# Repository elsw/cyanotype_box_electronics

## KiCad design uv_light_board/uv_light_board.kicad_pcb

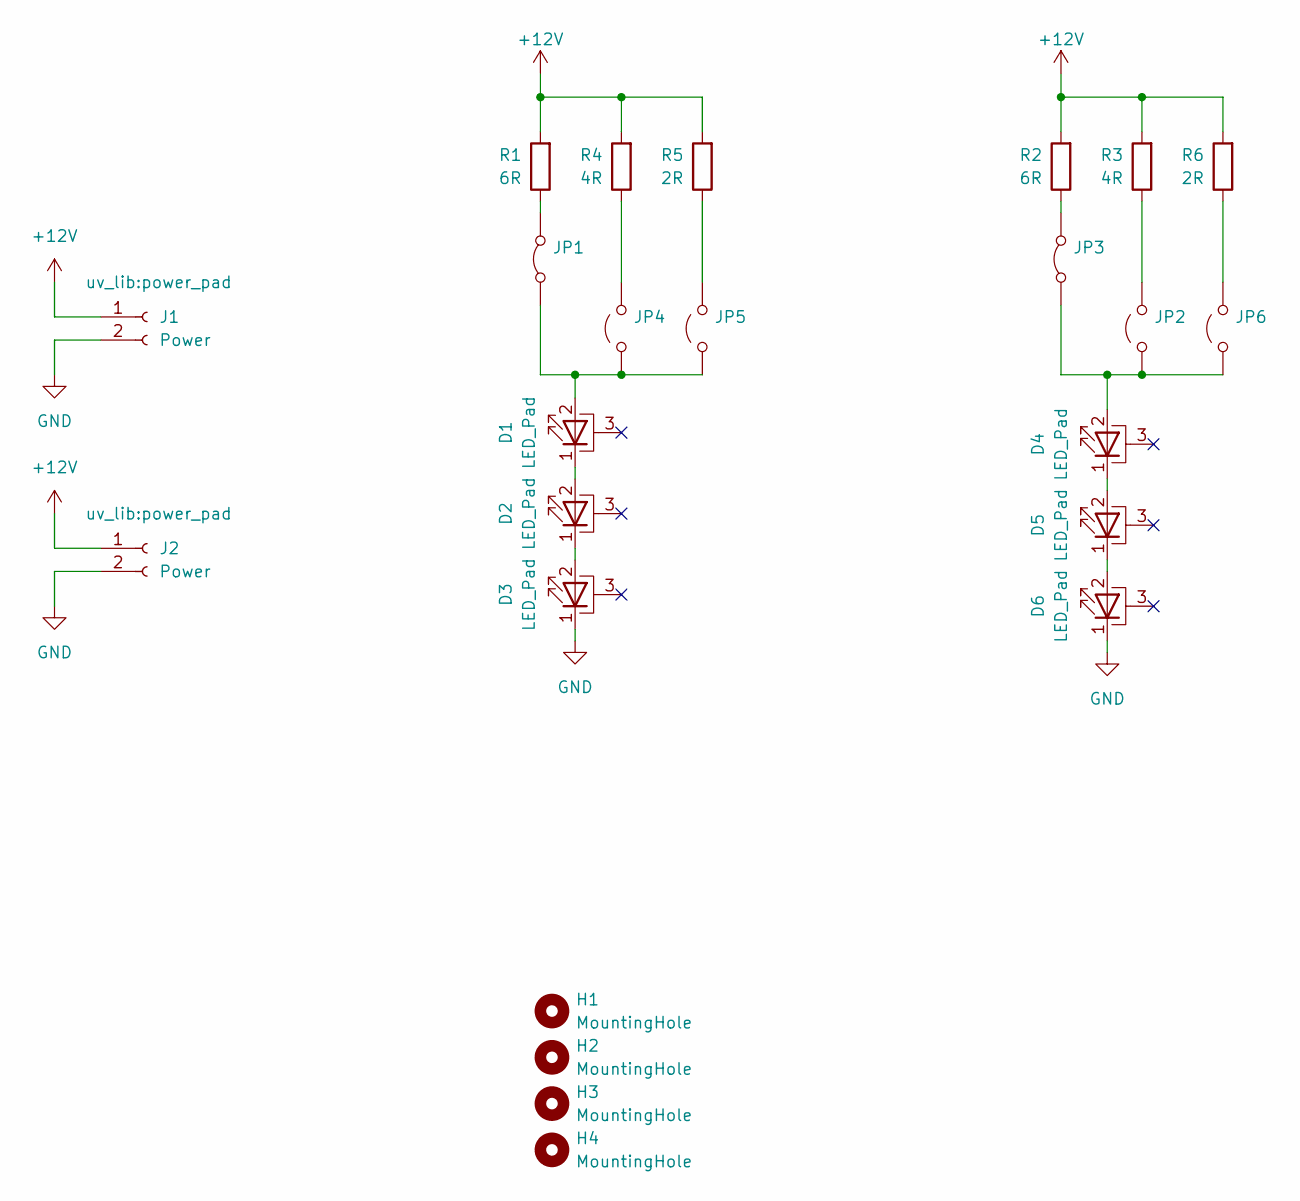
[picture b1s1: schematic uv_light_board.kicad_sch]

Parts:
D1, D2, D3, D4, D5, D6: LED_Pad; SMD3535-3P; JLCPCB Part C2833503
H1, H2, H3, H4: MountingHole; MountingHole_3.2mm_M3
J1, J2: Power; power_pad
JP1, JP3: Jumper_2_Bridged; SolderJumper-2_P1.3mm_Bridged2Bar_Pad1.0x1.5mm
JP2, JP4, JP5, JP6: Jumper_2_Open; SolderJumper-2_P1.3mm_Open_Pad1.0x1.5mm
R1, R2: 6R; R_2512_6332Metric; JLCPCB Part C2765522
R3, R4: 4R; R_2512_6332Metric; JLCPCB Part C39356
R5, R6: 2R; R_2512_6332Metric; JLCPCB Part C49298

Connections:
+12V: J1.1, J2.1, R1.2, R2.2, R3.2, R4.2, R5.2, R6.2
GND: D3.1 (K), D6.1 (K), J1.2, J2.2
unnamed: D1.2 (A), JP1.1 (A), JP4.1 (A), JP5.1 (A)
unnamed: D1.1 (K), D2.2 (A)
unnamed: D2.1 (K), D3.2 (A)
unnamed: D4.2 (A), JP2.1 (A), JP3.1 (A), JP6.1 (A)
unnamed: D4.1 (K), D5.2 (A)
unnamed: D5.1 (K), D6.2 (A)
unnamed: JP1.2 (B), R1.1
unnamed: JP2.2 (B), R3.1
unnamed: JP3.2 (B), R2.1
unnamed: JP4.2 (B), R4.1
unnamed: JP5.2 (B), R5.1
unnamed: JP6.2 (B), R6.1

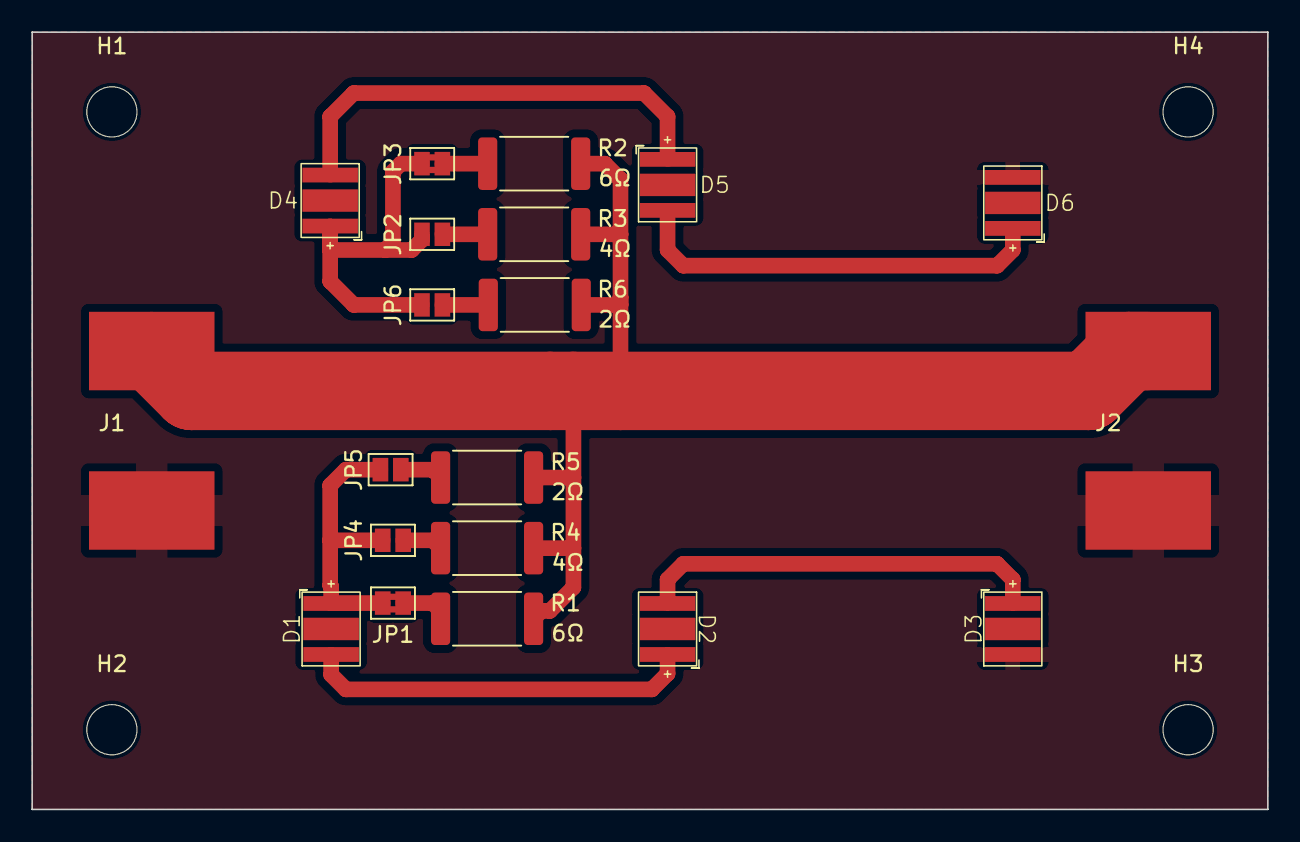
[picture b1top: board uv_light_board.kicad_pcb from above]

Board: 2 copper layers, 78.7 x 49.5 mm, 24 parts (0 on the bottom side), 14 nets.

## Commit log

2026-03-18 Replacing the UV led with an SMD LED we can buy PnP
2026-03-18 Adding part numbers to schematic
2026-03-23 Adding more resistor choices to light PCB, tweaking LED footprint
2026-03-24 Adding 3rd tuning resistor, fixing footprints on PCB
2026-05-08 Swapped pins for safety and en, added PWM to en pin
2026-05-13 Removed power select state and changed to fixed power at 50% PWM
2026-05-14 fixing bug limiting exposure time to 65 seconds
